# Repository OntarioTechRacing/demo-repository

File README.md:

# Welcome to your organization's demo respository
This code repository (or "repo") is designed to demonstrate the best GitHub has to offer with the least amount of noise.

The repo includes an `index.html` file (so it can render a web page), two GitHub Actions workflows, and a CSS stylesheet dependency.

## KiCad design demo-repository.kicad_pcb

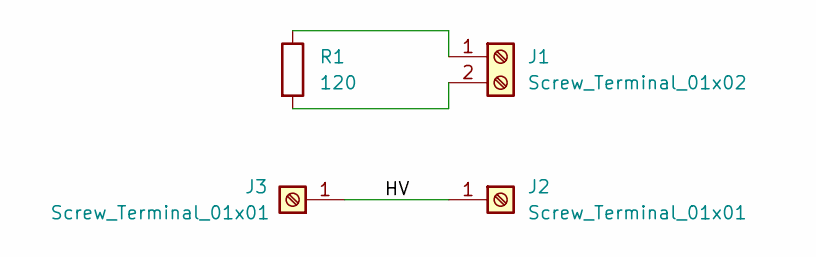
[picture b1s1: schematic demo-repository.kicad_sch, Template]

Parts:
J1: Screw_Terminal_01x02; PinHeader_1x02_P2.54mm_Vertical
J2, J3: Screw_Terminal_01x01; PinHeader_1x01_P2.54mm_Vertical
R1: 120; R_0603_1608Metric

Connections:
/HV: J2.1, J3.1
unnamed: J1.1, R1.1
unnamed: J1.2, R1.2

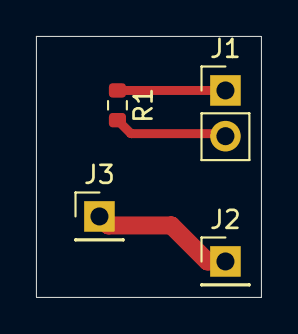
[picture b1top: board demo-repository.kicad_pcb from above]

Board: 4 copper layers, 12.5 x 14.5 mm, 4 parts (0 on the bottom side), 3 nets.

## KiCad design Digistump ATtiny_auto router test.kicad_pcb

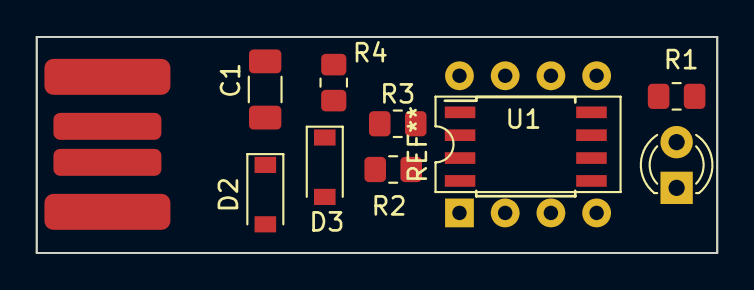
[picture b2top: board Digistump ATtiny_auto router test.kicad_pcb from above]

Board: 2 copper layers, 37.8 x 12.0 mm, 10 parts (0 on the bottom side), 8 nets, no tracks yet.

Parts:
C1: 100n; C_1206_3216Metric_Pad1.33x1.80mm_HandSolder
D1: LED; LED_D3.0mm
D2, D3: 3V6; D_SOD-123
R1: 330R; R_0805_2012Metric_Pad1.20x1.40mm_HandSolder
R2, R3: 68R; R_0805_2012Metric_Pad1.20x1.40mm_HandSolder
R4: 1k5; R_0805_2012Metric_Pad1.20x1.40mm_HandSolder
U1: ATtiny85; SOIC-8W_5.3x5.3mm_P1.27mm
U2: USB-PCB; USB-A-PCB

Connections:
+5V: C1.1, R4.2, U1.8 (VCC), U2.1 (VBUS)
GND: C1.2, D1.1 (K), D2.2 (A), D3.2 (A), U1.4 (GND), U2.4 (GND)
unnamed: D1.2 (A), R1.1
unnamed: D2.1 (K), R2.1, R4.1, U2.2 (D-)
unnamed: D3.1 (K), R3.1, U2.3 (D+)
unnamed: R2.2, U1.2 (XTAL1/PB3)
unnamed: R3.2, U1.3 (XTAL2/PB4)
unnamed: R1.2, U1.6 (PB1)

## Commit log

2024-04-20 Add workflow badges to README
2024-06-27 Create main.py to test workflow
2024-06-27 Update main.py for testing
2024-06-27 Update black-linter.yml for checking
2024-06-27 Update main.py to test Black
2024-06-27 Test bad formatting
2024-06-27 Refresh main.py changes for workflow
2024-06-27 Edit main.py for PR (again)
2024-06-28 Test workflow on PR (yes again)
2024-06-28 Update black-linter.yml back to simple
2024-06-28 Update black-linter.yml (please work)
2024-06-28 Update main.py (4 please work)
2024-06-28 Fix attempt for black-linter.yml
2024-06-28 Update black-linter.yml (ok just work)
2024-06-28 hope
2024-06-28 Try black diff annotations
2024-06-28 Add review annotations attempt
2024-06-28 Prove fix of main.py
2024-06-28 test break
2024-06-28 test fix
2024-07-02 Update issue templates
2024-07-06 Try new library workflows
2024-07-06 Fix env secrets pass
2024-07-08 Add example KiCad project
2024-07-08 Update to KiCad 8
2024-07-08 Update workflow and proj files
2024-07-08 Move config file location
2024-07-08 Update kibot.yaml workflow
2024-07-08 Attempt kibot config fix
2024-07-08 Again fix attempt
2024-07-08 Fix schematic and pcb paths
2024-07-08 Fix bad file path
2024-07-08 Update for KiCad 8 schematic file extensions
2024-07-08 Update workflow
2024-07-08 Reimplement specific file paths
2024-07-08 Simplified configs
2024-07-09 Test no needs lock workflow
2024-07-09 Remove old project
2024-07-09 Add new KiCad project
2024-07-09 Adjust for KiBot
2024-07-11 Update workflow for repo name structure
2024-07-11 Remove specified PCB and schematic files
2024-07-11 Fix missed file specification from last commit
2024-07-11 Test for custom DRC checker rules
2024-07-11 Improve workflow format
2024-07-11 Fix KiBot skips
2024-07-11 Comment out filters and update preflight syntax
2024-07-11 Match syntax with config and update formatting
2024-07-11 Improve configs
2024-07-11 Final cleanup
2024-07-11 Improve naming
